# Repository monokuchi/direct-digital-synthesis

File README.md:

# direct-digital-synthesis
Implements a simple signal generator using the direct digital synthesis (DDS) technique on a ARM7 core based processor

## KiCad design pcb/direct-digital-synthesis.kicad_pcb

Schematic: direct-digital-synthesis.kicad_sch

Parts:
C1, C25, C26, C27, C32, C37, C41, C42, C44, C45, C46, C54, C55, C64, C65, C70: 10u; C_0805_2012Metric
C2, C3, C4, C5, C7, C8, C9, C10, C11, C12, C13, C14, C16, C17, C19, C21, C22, C29, C30, C33, C34, C36, C56, C57, C58, C61, C62, C66, C69: 1u; C_0603_1608Metric
C6, C15, C23, C24, C28, C31, C35, C39, C48, C49, C52, C53, C63, C67, C68, C73, C74, C75, C76, C77, C78, C79, C80, C81, C82: 100n; C_0603_1608Metric
C18, C20: 2u2; C_0603_1608Metric
C38, C40: 10n; C_0603_1608Metric
C43: 20p; C_0603_1608Metric
C47: 4p7; C_0603_1608Metric
C50, C51: 22u; C_0805_2012Metric
C59, C71: 220p; C_0603_1608Metric
C60, C72: 470p; C_0603_1608Metric
D1: VCAN16A2-03GHE3-08; SOT65P230X110-3N; Manufacturer_Part_Number VCAN16A2-03GHE3-08; Mouser Part Number 78-VCAN16A203GHE3-08
FID1, FID2, FID3, FID4, FID5, FID6: Fiducial; Fiducial_1mm_Mask2mm
FID7: Fiducial; Fiducial_0.5mm_Mask1mm
H1, H2, H3, H4: MountingHole_Pad; MountingHole_4.3mm_M4_Pad_Via
IC1: IS42S16160J-7TLI; SOP80P1176X120-54N; Manufacturer_Part_Number IS42S16160J-7TLI; Mouser Part Number 870-IS42S16160J-7TLI
J1: TagConnect_TC2030; Tag-Connect_TC2030-IDC-FP_2x03_P1.27mm_Vertical
J2: Barrel_Jack_Switch; BarrelJack_Horizontal
J3: MEM2061-01-188-00-A; MEM20610118800A; Manufacturer_Part_Number MEM2061-01-188-00-A; Mouser Part Number 640-MEM20610118800A
J4: BNC_Connector; SMA_Molex_73251-1153_EdgeMount_Horizontal
J5: Conn_01x07_Socket; PinSocket_1x07_P2.54mm_Vertical
JP1, JP2, JP3, JP4, JP5: ME-100
L1: 6u8; ASPIAIG-F6060
LED1: IN-S66TBTRGB; INS66TBTRGB; Manufacturer_Part_Number IN-S66TBTRGB; Mouser Part Number 743-IN-S66TBTRGB
Q1: PMPB27EPZ; DFN-2020MD-6; Mouser Part Number 771-PMPB27EPZ
R1, R2, R3, R4, R5, R6, R7, R8, R9, R10, R11, R12, R13, R14, R15, R16, R17, R18, R19, R20, R21, R22, R23, R24, R25, R26, R27, R28, R29, R30, R31, R32, R33, R44, R45, R46, R47, R48, R49, R50, R51, R52, R53, R54, R55, R56, R57, R58, R59, R60, R61, R62, R63, R64, R71, R72, R73, R74, R75, R76, R77, R78, R79, R80, R81, R82, R83, R84, R85, R86, R87, R88: 22R; R_0603_1608Metric
R34, R42, R91, R93, R94, R95, R96: 10k; R_0603_1608Metric
R35, R38, R40: 100k; R_0603_1608Metric
R36: 43k2; R_0603_1608Metric
R37, R39: 909k; R_0603_1608Metric
R41, R43: 20k; R_0603_1608Metric
R65, R89: 59R; R_0603_1608Metric
R66, R90: 40R2; R_0603_1608Metric
R67, R68, R69: 100R; R_0603_1608Metric
R70, R92: 50k; R_0603_1608Metric
S1: L102021ML04Q; PARTREV N/A
SW1, SW2: SW_Push; SW_PUSH_6mm
TP1, TP2, TP3, TP4, TP5, TP6, TP7, TP8, TP9, TP10, TP11, TP12, TP13, TP14, TP15, TP16: GND; TestPoint_Keystone_5000-5004_Miniature
TP17: MCU_NRST; TestPoint_Keystone_5000-5004_Miniature
TP18: POWER_+15V; TestPoint_Keystone_5000-5004_Miniature
TP19: POWER_+10V; TestPoint_Keystone_5000-5004_Miniature
TP20: POWER_-12V; TestPoint_Keystone_5000-5004_Miniature
TP21: POWER_+12V; TestPoint_Keystone_5000-5004_Miniature
TP22: POWER_+3V3; TestPoint_Keystone_5000-5004_Miniature
U1: STM32H750IBT6; LQFP-176_24x24mm_P0.5mm
U2, U3: PCHCS541QWRKSRQ1; RKS0020B_VQFN_TEX-M
U4: AD5445YCPZ; CP_20_1_ADI-M
U5: LTC3260EDE-PBF; DFN-14_DE_LIT-M
U6: REF5010AID; D8-M
U7: LMR36015FBRNXR; RNX0012B
U8, U9: AD8066ARZ-R7; R_8_ADI-M
U10: PEC12R-3225F-S0024; PEC12R3225FS0024; Manufacturer_Part_Number PEC12R-3225F-S0024; Mouser Part Number 652-PEC12R3225FS0024
U11: MCP45HV51-ST; TSSOP-14_4.4x5mm_P0.65mm
U12: TLV07IDR; DGK0008A_N
Y1: ECS-2520MVQ-240-BS-TR; ECS2520MVQ240BSTR; Manufacturer_Part_Number ECS-2520MVQ-240-BS-TR

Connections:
+3.3V: C1.1, C2.1, C3.1, C4.1, C5.1, C6.1, C7.1, C8.1, C9.1, C10.1, C11.1, C12.1, C13.1, C14.1, C16.1, C17.1, C19.1, C21.1, C22.1, C23.1, C24.1, C27.1, C29.1, C53.1, C54.1, C55.1, C56.1, C57.1, C58.1, C61.1, C62.1, C66.1, C69.1, C70.1, C73.2, C76.1, IC1.1 (VDD_1), IC1.3 (VDDQ_1), IC1.9 (VDDQ_2), IC1.14 (VDD_2), IC1.27 (VDD_3), IC1.43 (VDDQ_3), IC1.49 (VDDQ_4), J1.1 (VCC), J3.P4 (VDD), J5.1, JP5.2 (B), LED1.1 (COM+), R70.2, R92.2, R93.2, R94.2, U1.6 (VBAT), U1.15 (VDD), U1.23 (VDD), U1.36 (VDD), U1.38 (VREF+), U1.39 (VDDA), U1.49 (VDD), U1.62 (VDD), U1.72 (VDD), U1.82 (VDD), U1.91 (VDD), U1.103 (VDD), U1.114 (VDD33_USB), U1.127 (VDD), U1.136 (VDD), U1.149 (VDD), U1.159 (VDD), U1.171 (PDR_ON), U1.172 (VDD), U2.20 (VCC), U3.20 (VCC), U4.16 (VDD), U11.1 (VL), Y1.4 (VDD)
+12V: C44.1, C48.1, C64.1, C67.1, C78.1, C82.1, JP4.2 (B), U8.8 (V+), U9.8 (V+), U11.14 (V+), U12.7 (V+)
+15V: C35.1, D1.1, J2.1, Q1.4 (S), Q1.8 (S), R34.1
-12V: C45.2, C49.2, C65.2, C68.2, C77.2, JP3.2 (B), U8.4 (V-), U9.4 (V-), U11.10 (V-)
/CHGPMP_+BYP: C40.1, U5.14 (BYP+)
/CHGPMP_+C: C30.1, U5.8 (C+)
/CHGPMP_+LDO: C46.1, JP4.1 (A), R39.1, TP21.1, U5.10 (LDO+)
/CHGPMP_-BYP: C38.1, U5.3 (BYP-)
/CHGPMP_-C: C30.2, U5.7 (C-)
/CHGPMP_-LDO: C42.1, JP3.1 (A), R37.1, TP20.1, U5.5 (LDO-)
/CHGPMP_VOUT: C37.1, U5.6 (VOUT)
/DAC.DB0: R33.2, U4.13 (DB0)
/DAC.DB1: R32.2, U4.12 (DB1)
/DAC.DB2: R31.2, U4.11 (DB2)
/DAC.DB3: R30.2, U4.10 (DB3)
/DAC.DB4: R29.2, U4.9 (DB4)
/DAC.DB5: R28.2, U4.8 (DB5)
/DAC.DB6: R27.2, U4.7 (DB6)
/DAC.DB7: R26.2, U4.6 (DB7)
/DAC.DB8: R25.2, U4.5 (DB8)
/DAC.DB9: R24.2, U4.4 (DB9)
/DAC.DB10: R23.2, U4.3 (DB10)
/DAC.DB11: R22.2, U4.2 (DB11)
/DAC_IOUT1: C47.2, U4.19 (IOUT1), U8.2 (IN-)
/DAC_NCS: R21.2, U4.14 (CS*)
/DAC_RFB: C47.1, R42.1, U4.18 (RFB), U8.1
/DISP_CLK: J5.4, R19.2
/DISP_CS: J5.3, U1.50 (PA4)
/DISP_DC: J5.5, U1.52 (PA6)
/DISP_DIN: J5.6, U1.53 (PA7)
/DISP_NRST: J5.7, U1.54 (PC4)
/DPOT_NSHDN: U1.153 (PG10), U11.8 (~SHDN)
/DPOT_P0W: U11.12 (P0W), U12.3 (IN+)
/DPOT_SCL: U1.164 (PB6), U11.2 (SCL)
/DPOT_SDA: U1.165 (PB7), U11.4 (SDA)
/MCU_DAC.DB0: R6.2, U3.9 (A8)
/MCU_DAC.DB1: R7.2, U3.8 (A7)
/MCU_DAC.DB2: R8.2, U3.7 (A6)
/MCU_DAC.DB3: R9.2, U3.6 (A5)
/MCU_DAC.DB4: R10.2, U3.5 (A4)
/MCU_DAC.DB5: R11.2, U3.4 (A3)
/MCU_DAC.DB6: R12.2, U3.3 (A2)
/MCU_DAC.DB7: R13.2, U3.2 (A1)
/MCU_DAC.DB8: R14.2, U2.9 (A8)
/MCU_DAC.DB9: R15.2, U2.8 (A7)
/MCU_DAC.DB10: R16.2, U2.7 (A6)
/MCU_DAC.DB11: R17.2, U2.6 (A5)
/MCU_DAC_NCS: R18.2, U2.2 (A1)
/MCU_LED_B: R69.2, U1.88 (PH11)
/MCU_LED_G: R68.2, U1.87 (PH10)
/MCU_LED_R: R67.2, U1.86 (PH9)
/MCU_NRST: C15.1, R1.2, TP17.1, U1.31 (NRST)
/MCU_OSC_IN: R5.2, U1.29 (PH0)
/MCU_SWCLK: R2.2, U1.137 (PA14)
/MCU_SWDIO: R3.2, U1.124 (PA13)
/MCU_SWO: R4.2, U1.161 (PB3)
/OPAMP_FILT_VOUT: C72.2, J4.1 (In), U9.6 (IN-), U9.7
/OPAMP_GAIN_VOUT: R43.2, R65.1, U8.7
/OPAMP_VREF: C36.1, R41.1, U4.17 (VREF), U12.2 (IN-), U12.6
/PMOS_DRAIN: D1.2, JP1.1 (A), Q1.1 (D), Q1.2 (D), Q1.5 (D), Q1.6 (D), Q1.7 (D), TP18.1
/POWER_SWITCH_+15V: C25.1, C26.1, C28.2, C31.2, C32.1, JP1.2 (B), U5.1 (EN+), U5.9 (VIN), U5.11 (EN-), U6.2 (VIN), U7.2 (VIN), U7.9 (EN), U7.10 (VIN)
/SDRAM.A0: R44.1, U1.16 (PF0)
/SDRAM.A1: R45.1, U1.17 (PF1)
/SDRAM.A2: R46.1, U1.18 (PF2)
/SDRAM.A3: R47.1, U1.19 (PF3)
/SDRAM.A4: R48.1, U1.20 (PF4)
/SDRAM.A5: R49.1, U1.21 (PF5)
/SDRAM.A6: R50.1, U1.60 (PF12)
/SDRAM.A7: R51.1, U1.63 (PF13)
/SDRAM.A8: R52.1, U1.64 (PF14)
/SDRAM.A9: R53.1, U1.65 (PF15)
/SDRAM.A10: R54.1, U1.66 (PG0)
/SDRAM.A11: R55.1, U1.67 (PG1)
/SDRAM.A12: R56.1, U1.106 (PG2)
/SDRAM.BA0: R57.1, U1.108 (PG4)
/SDRAM.BA1: R58.1, U1.109 (PG5)
/SDRAM.CKE: R60.1, U1.35 (PC3_C)
/SDRAM.CLK: R59.1, U1.112 (PG8)
/SDRAM.DQ0: R71.1, U1.104 (PD14)
/SDRAM.DQ1: R72.1, U1.105 (PD15)
/SDRAM.DQ2: R73.1, U1.142 (PD0)
/SDRAM.DQ3: R74.1, U1.143 (PD1)
/SDRAM.DQ4: R75.1, U1.68 (PE7)
/SDRAM.DQ5: R76.1, U1.69 (PE8)
/SDRAM.DQ6: R77.1, U1.70 (PE9)
/SDRAM.DQ7: R78.1, U1.73 (PE10)
/SDRAM.DQ8: R79.1, U1.74 (PE11)
/SDRAM.DQ9: R80.1, U1.75 (PE12)
/SDRAM.DQ10: R81.1, U1.76 (PE13)
/SDRAM.DQ11: R82.1, U1.77 (PE14)
/SDRAM.DQ12: R83.1, U1.78 (PE15)
/SDRAM.DQ13: R84.1, U1.96 (PD8)
/SDRAM.DQ14: R85.1, U1.97 (PD9)
/SDRAM.DQ15: R86.1, U1.98 (PD10)
/SDRAM.DQMH: R88.1, U1.170 (PE1)
/SDRAM.DQML: R87.1, U1.169 (PE0)
/SDRAM.NCAS: R62.1, U1.160 (PG15)
/SDRAM.NCS: R64.1, U1.34 (PC2_C)
/SDRAM.NRAS: R61.1, U1.59 (PF11)
/SDRAM.NWE: R63.1, U1.32 (PC0)
/SD_CD: C63.1, J3.CD1 (CARD_DETECT_1), R70.1, U1.145 (PD3)
/SD_CLK: J3.P5 (CLK), R20.2
/SD_CMD: J3.P3 (CMD), U1.144 (PD2)
/SD_DAT0: J3.P7 (DAT0), U1.117 (PC8)
/SD_DAT1: J3.P8 (DAT1), U1.118 (PC9)
/SD_DAT2: J3.P1 (DAT2), U1.139 (PC10)
/SD_DAT3: J3.P2 (CD/DAT3), U1.140 (PC11)
/SMPS_BST: C39.1, U7.4 (BST)
/SMPS_FB: C43.1, R35.2, R36.1, U7.7 (FB)
/SMPS_SW: C39.2, L1.1, U7.3 (NC), U7.12 (SW)
/SMPS_VCC: C33.1, U7.5 (VCC)
/SMPS_VOUT: C43.2, C50.1, C51.1, C52.2, JP5.1 (A), L1.2, R35.1, TP22.1
/UI_ENC_A: C80.1, R95.2, U1.40 (PA0)
/UI_ENC_B: C81.1, R96.2, U1.41 (PA1)
/UI_ENC_SW: C74.1, R91.1, U1.43 (PH2)
/UI_SW_A: C75.1, SW1.2, U1.45 (PH4)
/UI_SW_B: C79.1, SW2.2, U1.46 (PH5)
/VREF_+10V: JP2.2 (B), U11.13 (P0A)
GND: C1.2, C2.2, C3.2, C4.2, C5.2, C6.2, C7.2, C8.2, C9.2, C10.2, C11.2, C12.2, C13.2, C14.2, C15.2, C16.2, C17.2, C18.2, C19.2, C20.2, C21.2, C22.2, C23.2, C24.2, C25.2, C26.2, C27.2, C28.1, C29.2, C31.1, C32.2, C33.2, C34.2, C36.2, C37.2, C38.2, C40.2, C41.2, C42.2, C44.2, C45.1, C46.2, C48.2, C49.1, C50.2, C51.2, C52.1, C53.2, C54.2, C55.2, C56.2, C57.2, C58.2, C59.2, C61.2, C62.2, C63.2, C64.2, C65.1, C66.2, C67.2, C68.1, C69.2, C70.2, C71.2, C73.1, C74.2, C75.2, C76.2, C77.1, C78.2, C79.2, C80.2, C81.2, C82.2, D1.3, H1.1, H2.1, H3.1, H4.1, IC1.6 (VSSQ_1), IC1.12 (VSSQ_2), IC1.28 (VSS_1), IC1.41 (VSS_2), IC1.46 (VSSQ_3), IC1.52 (VSSQ_4), IC1.54 (VSS_3), J1.5 (GND), J2.2, J3.CD2 (CARD_DETECT_2), J3.G1 (GND_1), J3.G2 (GND_2), J3.P6 (VSS), J4.2 (Ext), J5.2, R36.2, R38.2, R40.2, S1.3, SW1.1, SW2.1, TP1.1, TP2.1, TP3.1, TP4.1, TP5.1, TP6.1, TP7.1, TP8.1, TP9.1, TP10.1, TP11.1, TP12.1, TP13.1, TP14.1, TP15.1, TP16.1, U1.14 (VSS), U1.22 (VSS), U1.37 (VSSA), U1.48 (VSS), U1.61 (VSS), U1.71 (VSS), U1.90 (VSS), U1.102 (VSS), U1.113 (VSS), U1.126 (VSS), U1.135 (VSS), U1.148 (VSS), U1.158 (VSS), U1.166 (BOOT0), U2.1 (*OE1), U2.3 (A2), U2.4 (A3), U2.5 (A4), U2.10 (GND), U2.19 (*OE2), U2.21 (GND), U3.1 (*OE1), U3.10 (GND), U3.19 (*OE2), U3.21 (GND), U4.1 (GND), U4.15 (R/W*), U4.20 (IOUT2), U4.21 (EP), U5.2 (RT), U5.12 (MODE), U5.15 (EPAD), U6.4 (GND), U7.1 (PGND), U7.6 (AGND), U7.8 (PG), U7.11 (PGND), U8.3 (IN+), U8.5 (IN+), U10.2, U10.C1, U11.3 (A1), U11.5 (A0), U11.6 (~WLAT), U11.9 (DGND), U11.11 (P0B), U12.4 (V-), Y1.2 (GND)
unnamed: C18.1, U1.81 (VCAP)
unnamed: C20.1, U1.125 (VCAP)
unnamed: C60.1, R65.2, R66.1
unnamed: C72.1, R89.2, R90.1
unnamed: IC1.23 (A0), R44.2
unnamed: IC1.24 (A1), R45.2
unnamed: IC1.25 (A2), R46.2
unnamed: IC1.26 (A3), R47.2
unnamed: IC1.29 (A4), R48.2
unnamed: IC1.30 (A5), R49.2
unnamed: IC1.31 (A6), R50.2
unnamed: IC1.32 (A7), R51.2
unnamed: IC1.33 (A8), R52.2
unnamed: IC1.34 (A9), R53.2
unnamed: IC1.22 (A10), R54.2
unnamed: IC1.35 (A11), R55.2
unnamed: IC1.36 (A12), R56.2
unnamed: IC1.20 (BA0), R57.2
unnamed: IC1.21 (BA1), R58.2
unnamed: IC1.37 (CKE), R60.2
unnamed: IC1.38 (CLK), R59.2
unnamed: IC1.2 (DQ0), R71.2
unnamed: IC1.4 (DQ1), R72.2
unnamed: IC1.5 (DQ2), R73.2
unnamed: IC1.7 (DQ3), R74.2
unnamed: IC1.8 (DQ4), R75.2
unnamed: IC1.10 (DQ5), R76.2
unnamed: IC1.11 (DQ6), R77.2
unnamed: IC1.13 (DQ7), R78.2
unnamed: IC1.42 (DQ8), R79.2
unnamed: IC1.44 (DQ9), R80.2
unnamed: IC1.45 (DQ10), R81.2
unnamed: IC1.47 (DQ11), R82.2
unnamed: IC1.48 (DQ12), R83.2
unnamed: IC1.50 (DQ13), R84.2
unnamed: IC1.51 (DQ14), R85.2
unnamed: IC1.53 (DQ15), R86.2
unnamed: IC1.39 (DQMH), R88.2
unnamed: IC1.15 (DQML), R87.2
unnamed: IC1.17 (~CAS), R62.2
unnamed: IC1.19 (~CS), R64.2
unnamed: IC1.18 (~RAS), R61.2
unnamed: IC1.16 (~WE), R63.2
unnamed: J1.4 (SWCLK), R2.1
unnamed: J1.2 (SWDIO), R3.1
unnamed: J1.6 (SWO), R4.1
unnamed: J1.3 (~RESET), R1.1
unnamed: C41.1, JP2.1 (A), TP19.1, U6.6 (VOUT)
unnamed: LED1.3 (K_BLUE), R69.1
unnamed: LED1.4 (K_GREEN), R68.1
unnamed: LED1.2 (K_RED), R67.1
unnamed: C35.2, Q1.3 (G), R34.2, S1.2
unnamed: R91.2, R92.1, U10.1
unnamed: R93.1, R95.1, U10.A1
unnamed: R94.1, R96.1, U10.B1
unnamed: R19.1, U1.51 (PA5)
unnamed: R20.1, U1.141 (PC12)
unnamed: R18.1, U1.25 (PF7)
unnamed: R6.1, U1.131 (PI0)
unnamed: R7.1, U1.132 (PI1)
unnamed: R8.1, U1.133 (PI2)
unnamed: R9.1, U1.134 (PI3)
unnamed: R10.1, U1.173 (PI4)
unnamed: R11.1, U1.174 (PI5)
unnamed: R12.1, U1.175 (PI6)
unnamed: R13.1, U1.176 (PI7)
unnamed: R14.1, U1.7 (PI8)
unnamed: R15.1, U1.11 (PI9)
unnamed: R16.1, U1.12 (PI10)
unnamed: R17.1, U1.13 (PI11)
unnamed: R21.1, U2.18 (Y1)
unnamed: R22.1, U2.14 (Y5)
unnamed: R23.1, U2.13 (Y6)
unnamed: R24.1, U2.12 (Y7)
unnamed: R25.1, U2.11 (Y8)
unnamed: R26.1, U3.18 (Y1)
unnamed: R27.1, U3.17 (Y2)
unnamed: R28.1, U3.16 (Y3)
unnamed: R29.1, U3.15 (Y4)
unnamed: R30.1, U3.14 (Y5)
unnamed: R31.1, U3.13 (Y6)
unnamed: R32.1, U3.12 (Y7)
unnamed: R33.1, U3.11 (Y8)
unnamed: R39.2, R40.1, U5.13 (ADJ+)
unnamed: R37.2, R38.1, U5.4 (ADJ-)
unnamed: C34.1, U6.5 (TRIM/NR)
unnamed: R41.2, R42.2, R43.1, U8.6 (IN-)
unnamed: C59.1, R66.2, U9.3 (IN+)
unnamed: C60.2, R89.1, U9.1, U9.2 (IN-)
unnamed: C71.1, R90.2, U9.5 (IN+)
unnamed: R5.1, Y1.3 (OUTPUT)

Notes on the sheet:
Gain/DC Bias Stage
Push Buttons
Low Pass Filter
Transimpedance Amplifier
Precision Voltage Reference (+10VDC)
Rotary Encoder
Input DC Power Jack w/ Switch
DAC
Schmitt Trigger Buffers
Low Noise Dual Supply Inverting Charge Pump (+-12VDC)
SMPS (+3.3VDC)
Power Switch Requirements: Max Voltage Rating > 15VDC Max Current Rating > 600mA
1/8W rated current limiting resistors
Low Temperature Drift Precision Resistors
I2C Device Address is 0111 100b (Pg 51)
V_{out}=[+V_{ref} to -V_{ref}]
LDO_{vout}=VREF*(1+R1/R2) (For both + and - LDOs) VREF=1.2VDC, R1=909k, R2=100k LDO_{vout}=+-12.108VDC (Pg 10)
Micro SD Card
[Current Budget (3.3V Rail in Amps)] MCU: 0.620 Schmitt Trigger Buffers (x2): 0.0002 DAC: 0.005 Micro SD Card: 0.16 Rotary Encoder: 0.01 RGB LED: 0.06 Display: 0.06 Clock Oscillator: 0.01 SDRAM: 0.12 Total: 1.0452 Amps
Mounting Holes
List of voltages needed: +3.3VDC +12VDC -12VDC
Power Supply IC's already have built in in-rush current management so don't need to have external circuitry to handle sparking Ex (3.3VDC Rail): I_{inrush}=C_{load}*(dV/dt)=75 [uF] * (3.3/4 [ms])~=62 [mA] (4 ms rise time specified on Pg 13)
Low ESR VCAP Capacitors (<100 mOhms)
Display Connector
Place series termination resistors close to the driver output
Maximum Voltage: 16VDC
Output amplifier is meant to drive standard line level audio equipment which usually have a load impedance of ~600 Ohms. So power circuitry needs to be capable of supplying at least I=V/R -> I=10[V]/600[R]=16.67[mA]
OLED Display Resolution is 128x128 and 16 bits per pixel
The 10uF bypass capacitors on LDO+, LDO-, VIN should be low ESR Also make sure to choose max voltage rating of the capacitors high enough to prevent excessive capacitance loss (Pg 7)
Digital Potentiometer
ESR of Vout Bypass Capacitor must be within [1, 1.5] Ohms to ensure ouput stability
TVS Diode Protection
When SD card is inserted SD_CD is high and when SD card is not inserted SD_CD is low
Power
Relying on internal pull up resistors and ESD protection of STM32 MCU SD Clock Running at 40 MHz
Fiducials
Cutoff Frequency: f(-3dB) = 8.33 MHz Gain (Linear): 1 Number of Filter Stages: 2 Total Filter Order: 4 Q=0.72 Total Quiescient Current Draw: 14.8 mA
50 Ohm BNC Connector
Ground Test Points
Bypass Capacitors included to help mitgate noise

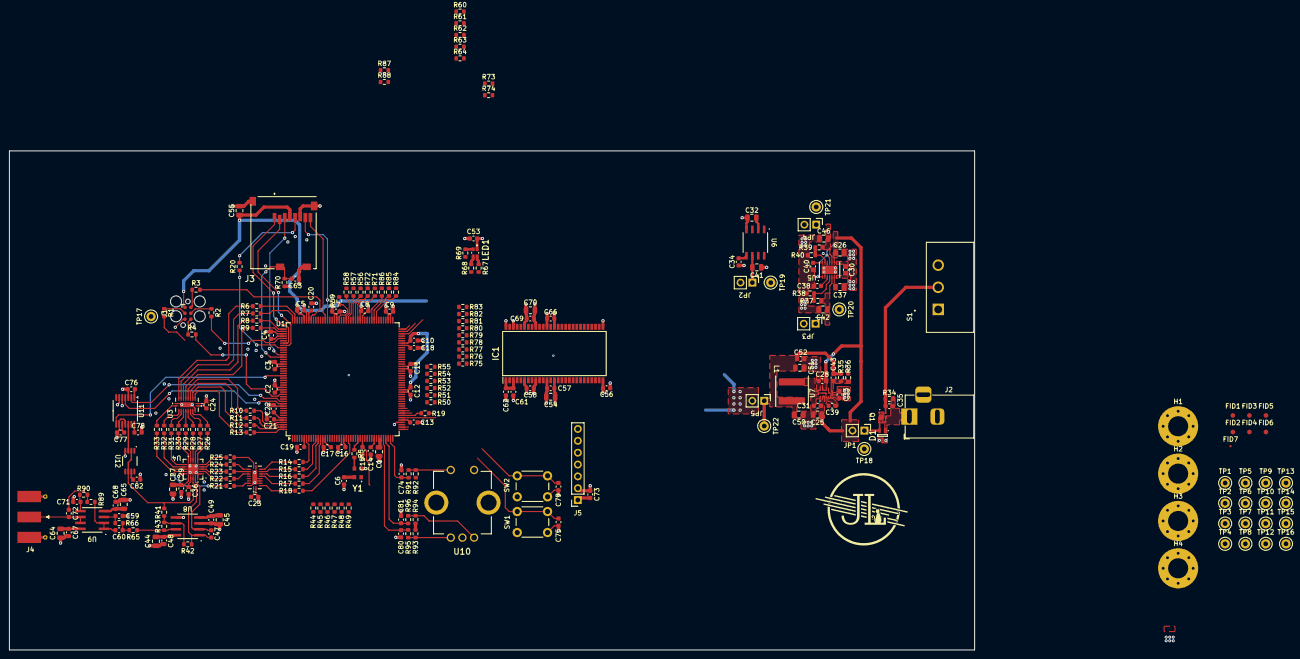
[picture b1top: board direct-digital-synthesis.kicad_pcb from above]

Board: 4 copper layers, 206.9 x 107.0 mm, 242 parts (0 on the bottom side), 210 nets.

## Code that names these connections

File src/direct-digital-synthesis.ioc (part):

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Mcu.Name=STM32H750IBTx
Mcu.Package=LQFP176
Mcu.UserName=STM32H750IBTx
PA1.GPIOParameters=GPIO_Speed,GPIO_Label
PA1.GPIO_Label=DAC_NCS
PA1.GPIO_Speed=GPIO_SPEED_FREQ_LOW
PA1.Signal=S_TIM2_CH2
PA13\ (JTMS/SWDIO).Mode=Trace_Asynchronous_SW
PA13\ (JTMS/SWDIO).Signal=DEBUG_JTMS-SWDIO
PA14\ (JTCK/SWCLK).Mode=Trace_Asynchronous_SW
PA14\ (JTCK/SWCLK).Signal=DEBUG_JTCK-SWCLK
PB3\ (JTDO/TRACESWO).Mode=Trace_Asynchronous_SW
PB3\ (JTDO/TRACESWO).Signal=DEBUG_JTDO-SWO
PC0.Signal=FMC_SDNWE
PC10.GPIOParameters=GPIO_PuPd,GPIO_Speed_High_Default
PC10.GPIO_PuPd=GPIO_PULLUP
PC10.GPIO_Speed_High_Default=GPIO_SPEED_FREQ_LOW
PC10.Mode=SD_4_bits_Wide_bus
PC10.Signal=SDMMC1_D2
PC11.GPIOParameters=GPIO_PuPd,GPIO_Speed_High_Default
PC11.GPIO_PuPd=GPIO_PULLUP
PC11.GPIO_Speed_High_Default=GPIO_SPEED_FREQ_LOW
PC11.Mode=SD_4_bits_Wide_bus
PC11.Signal=SDMMC1_D3
PC12.GPIOParameters=GPIO_Speed_High_Default
PC12.GPIO_Speed_High_Default=GPIO_SPEED_FREQ_LOW
PC12.Mode=SD_4_bits_Wide_bus
PC12.Signal=SDMMC1_CK
PC2_C.Mode=SdramChipSelect1_1
PC2_C.Signal=FMC_SDNE0
PC3_C.Mode=SdramChipSelect1_1
PC3_C.Signal=FMC_SDCKE0
PC8.GPIOParameters=GPIO_PuPd,GPIO_Speed_High_Default
PC8.GPIO_PuPd=GPIO_PULLUP
PC8.GPIO_Speed_High_Default=GPIO_SPEED_FREQ_LOW
PC8.Mode=SD_4_bits_Wide_bus
PC8.Signal=SDMMC1_D0
PC9.GPIOParameters=GPIO_PuPd,GPIO_Speed_High_Default
PC9.GPIO_PuPd=GPIO_PULLUP
PC9.GPIO_Speed_High_Default=GPIO_SPEED_FREQ_LOW
PC9.Mode=SD_4_bits_Wide_bus
PC9.Signal=SDMMC1_D1
PD0.Signal=FMC_D2_DA2
PD1.Signal=FMC_D3_DA3
PD10.Signal=FMC_D15_DA15
PD14.Signal=FMC_D0_DA0
PD15.Signal=FMC_D1_DA1
PD2.GPIOParameters=GPIO_PuPd,GPIO_Speed_High_Default
PD2.GPIO_PuPd=GPIO_PULLUP
PD2.GPIO_Speed_High_Default=GPIO_SPEED_FREQ_LOW
PD2.Mode=SD_4_bits_Wide_bus
PD2.Signal=SDMMC1_CMD
PD3.GPIOParameters=GPIO_Label
PD3.GPIO_Label=SD_NCD
PD3.Signal=GPIO_Input
PD8.Signal=FMC_D13_DA13
PD9.Signal=FMC_D14_DA14
PE0.Signal=FMC_NBL0
PE1.Signal=FMC_NBL1
PE10.Signal=FMC_D7_DA7
PE11.Signal=FMC_D8_DA8
PE12.Signal=FMC_D9_DA9
PE13.Signal=FMC_D10_DA10
PE14.Signal=FMC_D11_DA11
PE15.Signal=FMC_D12_DA12
PE7.Signal=FMC_D4_DA4
PE8.Signal=FMC_D5_DA5
PE9.Signal=FMC_D6_DA6
PF0.Signal=FMC_A0
PF1.Signal=FMC_A1
PF11.Signal=FMC_SDNRAS
PF12.Signal=FMC_A6
PF13.Signal=FMC_A7
PF14.Signal=FMC_A8
PF15.Signal=FMC_A9
PF2.Signal=FMC_A2
PF3.Signal=FMC_A3
PF4.Signal=FMC_A4
PF5.Signal=FMC_A5
PG0.Signal=FMC_A10
PG1.Signal=FMC_A11
PG15.Signal=FMC_SDNCAS
PG2.Signal=FMC_A12
PG4.Signal=FMC_A14_BA0
PG5.Signal=FMC_A15_BA1
PG8.Signal=FMC_SDCLK
PH0-OSC_IN\ (PH0).Mode=HSE-External-Clock-Source
PH0-OSC_IN\ (PH0).Signal=RCC_OSC_IN
PH2.GPIOParameters=GPIO_Label
PH2.GPIO_Label=STATUS_LED_R
PH2.Signal=GPIO_Output
PH3.GPIOParameters=GPIO_Label
PH3.GPIO_Label=STATUS_LED_G
PH3.Signal=GPIO_Output
PH4.GPIOParameters=GPIO_Label
PH4.GPIO_Label=STATUS_LED_B
PH4.Signal=GPIO_Output
PI0.GPIOParameters=GPIO_Speed,GPIO_Label
PI0.GPIO_Label=DAC_DB0
PI0.GPIO_Speed=GPIO_SPEED_FREQ_LOW
PI0.Signal=GPIO_Output
PI1.GPIOParameters=GPIO_Speed,GPIO_Label
PI1.GPIO_Label=DAC_DB1
PI1.GPIO_Speed=GPIO_SPEED_FREQ_LOW
PI1.Signal=GPIO_Output
PI10.GPIOParameters=GPIO_Speed,GPIO_Label
PI10.GPIO_Label=DAC_DB10
PI10.GPIO_Speed=GPIO_SPEED_FREQ_LOW
PI10.Signal=GPIO_Output
PI11.GPIOParameters=GPIO_Speed,GPIO_Label
PI11.GPIO_Label=DAC_DB11
PI11.GPIO_Speed=GPIO_SPEED_FREQ_LOW
PI11.Signal=GPIO_Output
PI2.GPIOParameters=GPIO_Speed,GPIO_Label
PI2.GPIO_Label=DAC_DB2
PI2.GPIO_Speed=GPIO_SPEED_FREQ_LOW
PI2.Signal=GPIO_Output
PI3.GPIOParameters=GPIO_Speed,GPIO_Label
PI3.GPIO_Label=DAC_DB3
PI3.GPIO_Speed=GPIO_SPEED_FREQ_LOW
PI3.Signal=GPIO_Output
PI4.GPIOParameters=GPIO_Speed,GPIO_Label
PI4.GPIO_Label=DAC_DB4
PI4.GPIO_Speed=GPIO_SPEED_FREQ_LOW
PI4.Signal=GPIO_Output
PI5.GPIOParameters=GPIO_Speed,GPIO_Label
PI5.GPIO_Label=DAC_DB5
PI5.GPIO_Speed=GPIO_SPEED_FREQ_LOW
PI5.Signal=GPIO_Output
PI6.GPIOParameters=GPIO_Speed,GPIO_Label
PI6.GPIO_Label=DAC_DB6
PI6.GPIO_Speed=GPIO_SPEED_FREQ_LOW
PI6.Signal=GPIO_Output
PI7.GPIOParameters=GPIO_Speed,GPIO_Label
PI7.GPIO_Label=DAC_DB7
PI7.GPIO_Speed=GPIO_SPEED_FREQ_LOW
PI7.Signal=GPIO_Output
PI8.GPIOParameters=GPIO_Speed,GPIO_Label
PI8.GPIO_Label=DAC_DB8
PI8.GPIO_Speed=GPIO_SPEED_FREQ_LOW
PI8.Signal=GPIO_Output
PI9.GPIOParameters=GPIO_Speed,GPIO_Label
PI9.GPIO_Label=DAC_DB9
PI9.GPIO_Speed=GPIO_SPEED_FREQ_LOW
PI9.Signal=GPIO_Output
RCC.HSE_VALUE=24000000
RCC.SYSCLKFreq_VALUE=480000000
RCC.SYSCLKSource=RCC_SYSCLKSOURCE_PLLCLK
board=custom

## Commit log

2024-11-30 script
2025-01-08 Updated pcb and src
2025-01-11 pcb update
2025-01-20 update pcb
2025-02-05 fixed sdram
